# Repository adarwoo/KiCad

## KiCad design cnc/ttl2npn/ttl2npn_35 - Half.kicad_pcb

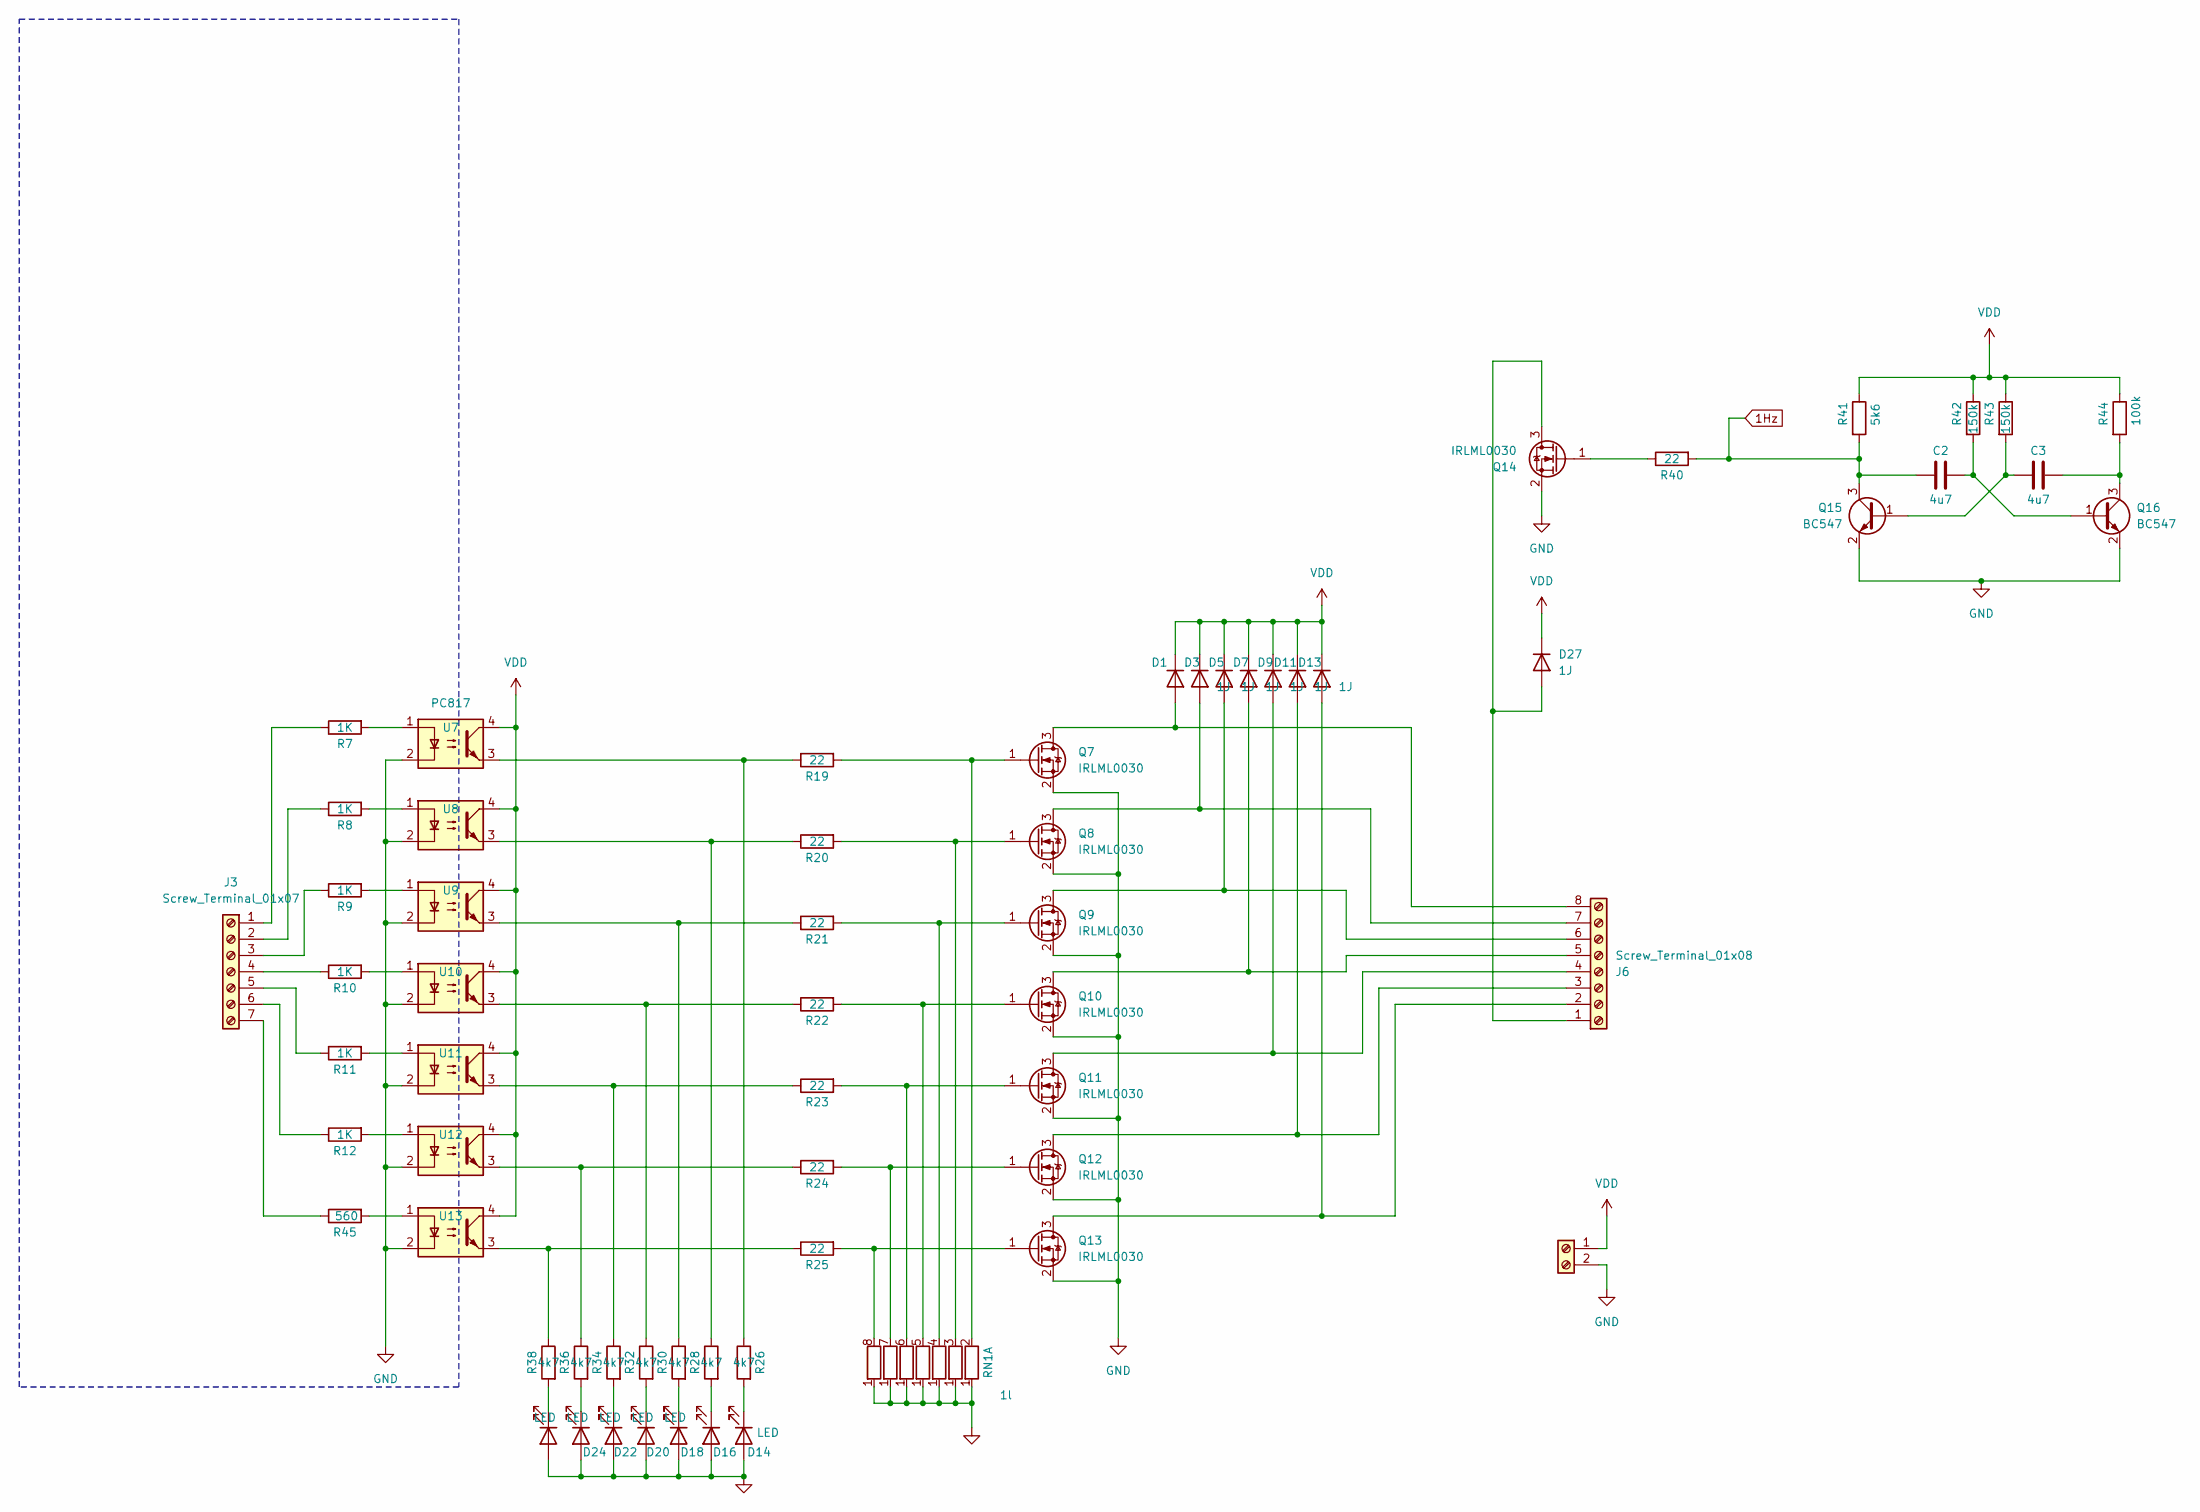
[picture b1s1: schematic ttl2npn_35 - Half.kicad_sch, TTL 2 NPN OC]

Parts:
C2, C3: 4u7; C_1206_3216Metric
D1, D3, D5, D7, D9, D11, D13, D27: 1J; D_MicroSMP_AK
D14, D16, D18, D20, D22, D24, D26: LED; LED_D3.0mm
J3: Screw_Terminal_01x07; PhoenixContact_MCV_1,5_7-G-3.81_1x07_P3.81mm_Vertical
J4: Screw_Terminal_01x02; PhoenixContact_MCV_1,5_2-G-3.81_1x02_P3.81mm_Vertical
J6: Screw_Terminal_01x08; PhoenixContact_MCV_1,5_8-G-3.81_1x08_P3.81mm_Vertical
Q7, Q8, Q9, Q10, Q11, Q12, Q13, Q14: IRLML0030; SOT-23
Q15, Q16: BC547; SOT-23
R7, R8, R9, R10, R11, R12: 1K; R_0805_2012Metric
R19, R20, R21, R22, R23, R24, R25, R40: 22; R_0805_2012Metric
R26, R28, R30, R32, R34, R36, R38: 4k7; R_0805_2012Metric
R41: 5k6; R_0805_2012Metric
R42, R43: 150k; R_0805_2012Metric
R44: 100k; R_0805_2012Metric
R45: 560; R_0805_2012Metric
RN1: 1l; R_Array_SIP8
U7, U8, U9, U10, U11, U12, U13: PC817; DIP-4_W7.62mm

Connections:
1Hz: C2.1, Q15.3 (C), R40.2, R41.2
GND: D14.2 (A), D16.2 (A), D18.2 (A), D20.2 (A), D22.2 (A), D24.2 (A), D26.2 (A), J4.2, Q7.2 (S), Q8.2 (S), Q9.2 (S), Q10.2 (S), Q11.2 (S), Q12.2 (S), Q13.2 (S), Q14.2 (S), Q15.2 (E), Q16.2 (E), RN1.1 (R1), U7.2, U8.2, U9.2, U10.2, U11.2, U12.2, U13.2
unnamed: D1.2 (A), J6.8, Q7.3 (D)
unnamed: D3.2 (A), J6.7, Q8.3 (D)
unnamed: D5.2 (A), J6.6, Q9.3 (D)
unnamed: D7.2 (A), J6.5, Q10.3 (D)
unnamed: D9.2 (A), J6.4, Q11.3 (D)
unnamed: D11.2 (A), J6.3, Q12.3 (D)
unnamed: D13.2 (A), J6.2, Q13.3 (D)
unnamed: D14.1 (K), R26.2
unnamed: D16.1 (K), R28.2
unnamed: D18.1 (K), R30.2
unnamed: D20.1 (K), R32.2
unnamed: D22.1 (K), R34.2
unnamed: D24.1 (K), R36.2
unnamed: D26.1 (K), R38.2
unnamed: D27.2 (A), J6.1, Q14.3 (D)
unnamed: J3.1, R7.1
unnamed: J3.2, R8.1
unnamed: J3.3, R9.1
unnamed: J3.4, R10.1
unnamed: J3.5, R11.1
unnamed: J3.6, R12.1
unnamed: J3.7, R45.1
unnamed: Q7.1 (G), R19.2, RN1.2 (R1.2)
unnamed: Q8.1 (G), R20.2, RN1.3 (R2.2)
unnamed: Q9.1 (G), R21.2, RN1.4 (R3.2)
unnamed: Q10.1 (G), R22.2, RN1.5 (R4.2)
unnamed: Q11.1 (G), R23.2, RN1.6 (R5.2)
unnamed: Q12.1 (G), R24.2, RN1.7 (R6.2)
unnamed: Q13.1 (G), R25.2, RN1.8 (R7.2)
unnamed: Q14.1 (G), R40.1
unnamed: C3.1, Q15.1 (B), R43.2
unnamed: C2.2, Q16.1 (B), R42.2
unnamed: C3.2, Q16.3 (C), R44.2
unnamed: R7.2, U7.1
unnamed: R8.2, U8.1
unnamed: R9.2, U9.1
unnamed: R10.2, U10.1
unnamed: R11.2, U11.1
unnamed: R12.2, U12.1
unnamed: R19.1, R26.1, U7.3
unnamed: R20.1, R28.1, U8.3
unnamed: R21.1, R30.1, U9.3
unnamed: R22.1, R32.1, U10.3
unnamed: R23.1, R34.1, U11.3
unnamed: R24.1, R36.1, U12.3
unnamed: R25.1, R38.1, U13.3
unnamed: R45.2, U13.1
VDD: D1.1 (K), D3.1 (K), D5.1 (K), D7.1 (K), D9.1 (K), D11.1 (K), D13.1 (K), D27.1 (K), J4.1, R41.1, R42.1, R43.1, R44.1, U7.4, U8.4, U9.4, U10.4, U11.4, U12.4, U13.4

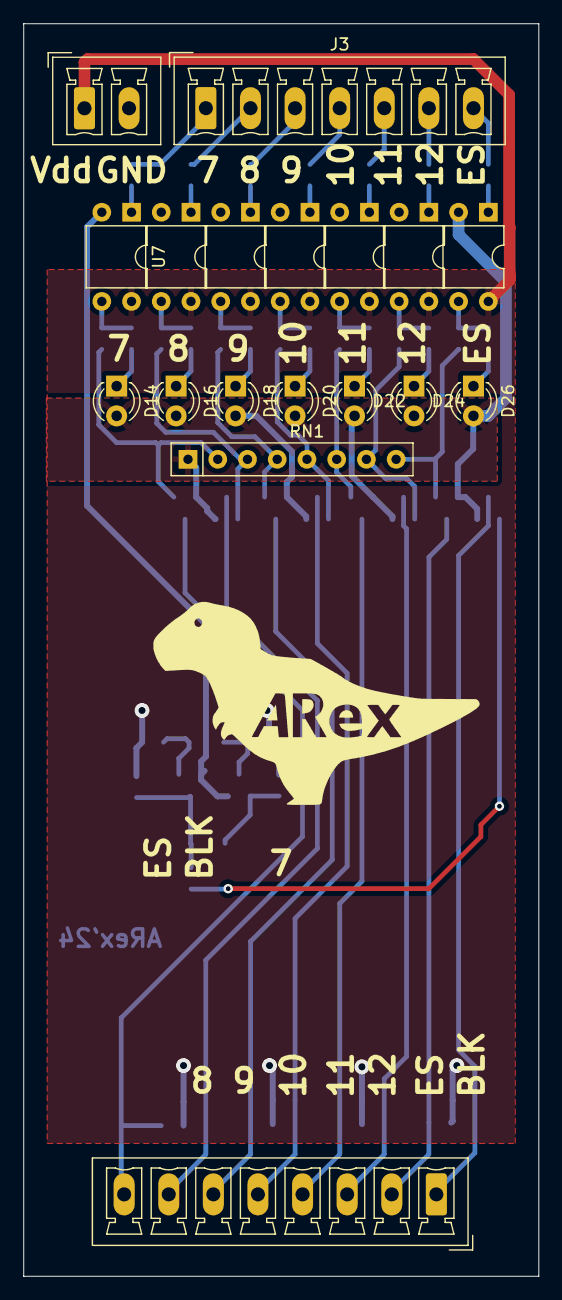
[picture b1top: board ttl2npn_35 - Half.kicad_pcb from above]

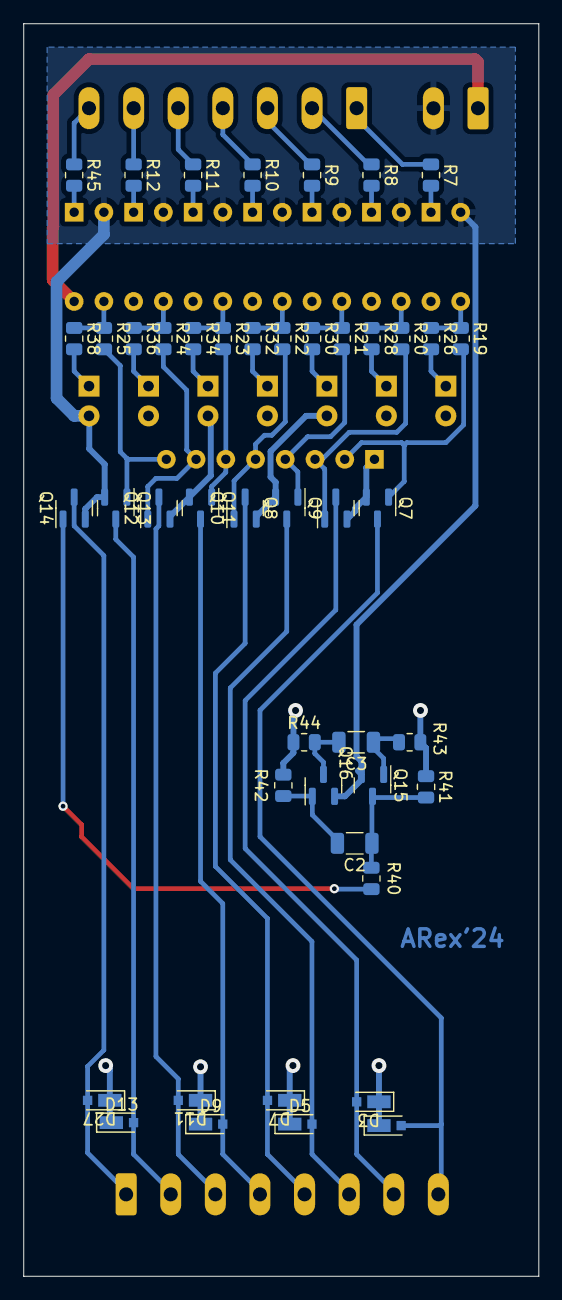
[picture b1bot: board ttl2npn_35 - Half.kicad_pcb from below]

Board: 2 copper layers, 44.0 x 107.0 mm, 64 parts (46 on the bottom side), 50 nets.

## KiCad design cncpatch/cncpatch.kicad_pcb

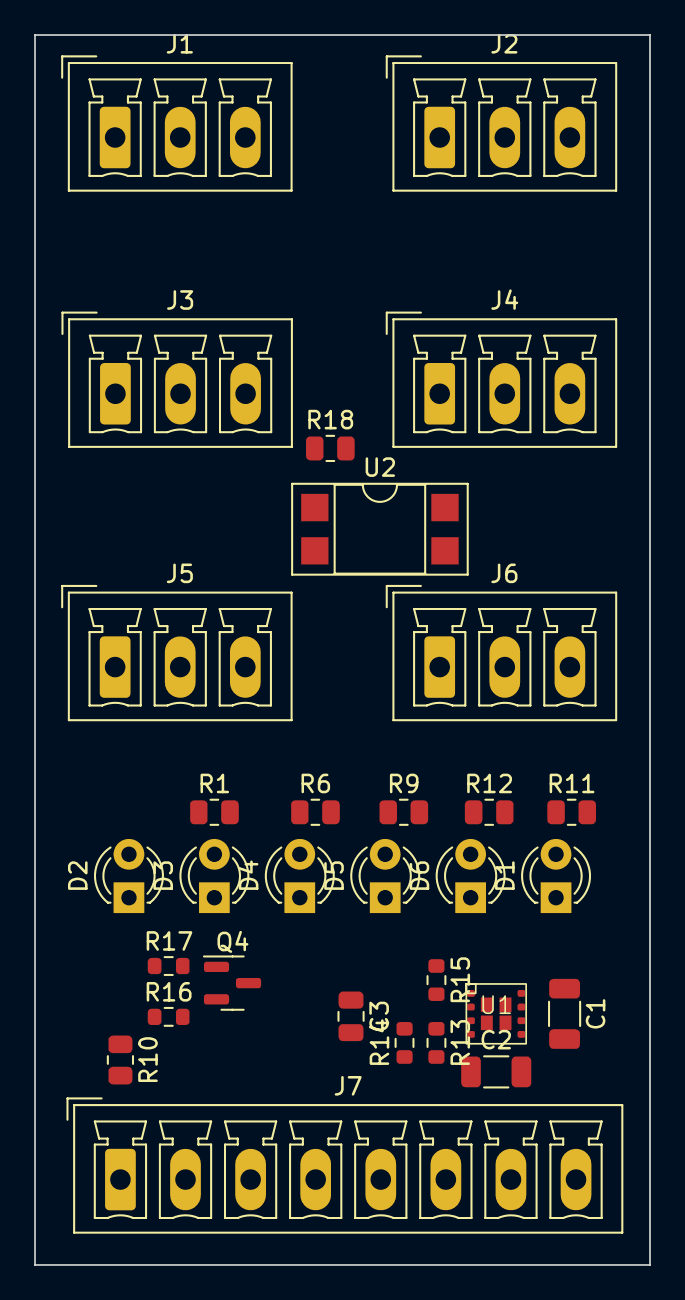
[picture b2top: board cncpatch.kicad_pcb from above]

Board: 2 copper layers, 36.0 x 72.0 mm, 31 parts (0 on the bottom side), 23 nets, no tracks yet.

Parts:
C1, C2: 22u; C_1206_3216Metric
C3: 3n3; C_0805_2012Metric
D1: RED; LED_D3.0mm
D2: LED; LED_D3.0mm
D3, D4, D5: GRN; LED_D3.0mm
D6: ORG; LED_D3.0mm
J1, J2, J3, J4, J5, J6: Conn_01x03_Socket; PhoenixContact_MCV_1,5_3-G-3.81_1x03_P3.81mm_Vertical
J7: Conn_01x08_Socket; PhoenixContact_MCV_1,5_8-G-3.81_1x08_P3.81mm_Vertical
Q4: AO3401A; SOT-23
R1, R6, R9, R10, R11, R18: 10k; R_0805_2012Metric
R12: 3k3; R_0805_2012Metric
R13, R16: 10k; R_0603_1608Metric
R14: 232k; R_0603_1608Metric
R15: 44k2; R_0603_1608Metric
R17: 22; R_0603_1608Metric
U1: MicroSiP
U2: PC817; DIP-4_W7.62mm_SMDSocket_SmallPads

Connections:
+5V: C2.1, J6.1, Q4.2 (S), R12.2, R13.2, R14.1, U1.4 (VOUT), U1.6 (VOS)
/LASER_EN: J6.2, Q4.3 (D)
/LASER_ON_OC: J7.7, R16.1, R17.1
/SPINDLE_STOP: J7.8, U2.4
/SPINDLE_STOP_OC: J2.2, U2.2
/TOUCH_OUT: D1.1 (K), J4.2, J7.6
/X_MASSO: J1.2, J7.3, R1.2
/Y_MASSO: J3.2, J7.4, R6.2
/Z_MASSO: J5.2, J7.5, R9.2
GND: C1.2, C2.2, C3.2, D2.1 (K), D3.1 (K), D4.1 (K), D5.1 (K), D6.1 (K), J1.3, J2.3, J3.3, J4.3, J5.3, J6.3, J7.2, R15.1, U1.5 (GND), U1.9 (GND), U2.3
unnamed: D1.2 (A), R11.1
unnamed: D2.2 (A), R10.1
unnamed: D3.2 (A), R1.1
unnamed: D4.2 (A), R6.1
unnamed: D5.2 (A), R9.1
unnamed: D6.2 (A), R12.1
unnamed: Q4.1 (G), R17.2
unnamed: R18.1, U2.1
unnamed: C1.1, U1.7 (EN), U1.8 (VIN)
unnamed: R14.2, R15.2, U1.2 (FB)
unnamed: R13.1, U1.3 (PG)
unnamed: C3.1, U1.1 (SS)
VDD: J1.1, J2.1, J3.1, J4.1, J5.1, J7.1, R10.2, R11.2, R16.2, R18.2

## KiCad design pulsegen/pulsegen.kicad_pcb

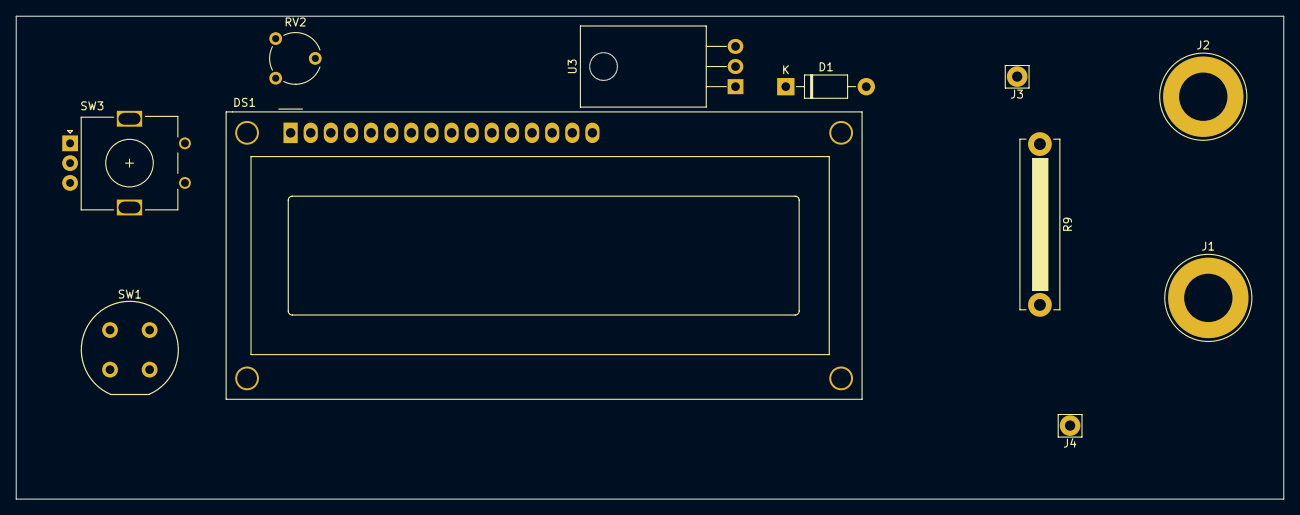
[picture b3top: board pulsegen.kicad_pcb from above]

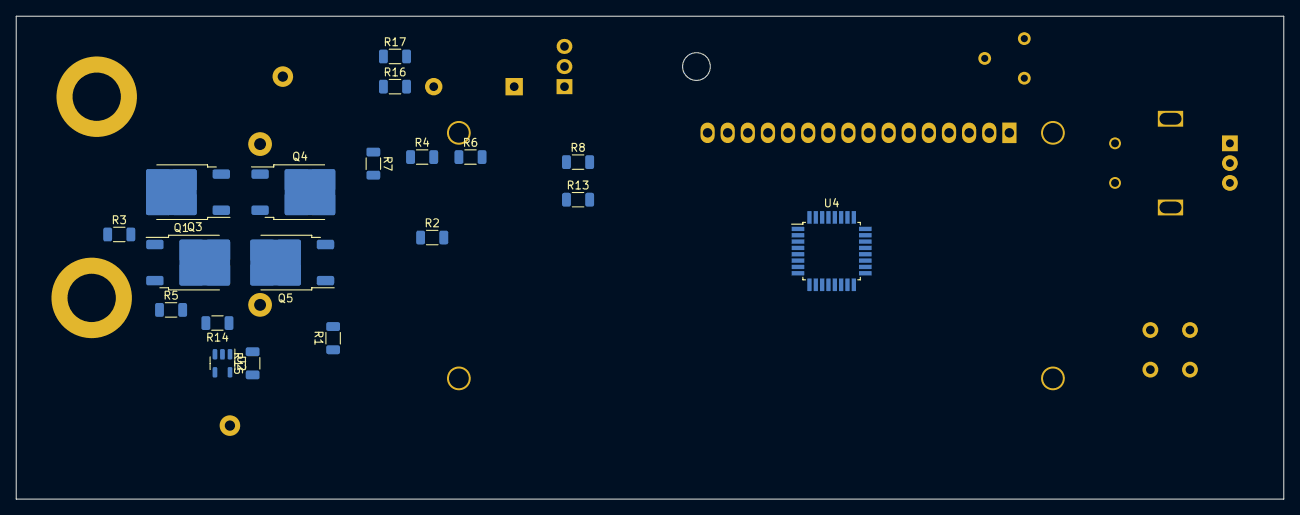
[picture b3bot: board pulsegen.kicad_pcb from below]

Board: 2 copper layers, 160.0 x 61.0 mm, 30 parts (19 on the bottom side), 31 nets, no tracks yet.

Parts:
D1: 1N4007; D_DO-41_SOD81_P10.16mm_Horizontal
DS1: WC1602A
J1, J2: Screw_Terminal_01x01; Banana_Jack_1Pin
J3, J4: Screw_Terminal_01x01; Pin_D1.3mm_L11.3mm_W2.8mm_Flat
Q1, Q4: QM6006D; TO-252-2
Q3, Q5: QM6015D; TO-252-2
R1, R2, R3, R4: 22; R_1206_3216Metric
R5, R6, R7, R8: 10k; R_1206_3216Metric
R9: 0.01 5W; R_Bare_Metal_Element_L21.3mm_W4.8mm_P20.30mm
R13, R15: 1k; R_1206_3216Metric
R14: 100k; R_1206_3216Metric
R16, R17: R; R_1206_3216Metric
RV2: R_Potentiometer; Potentiometer_Piher_PT-6-V_Vertical
SW1: SW_Push; Push_E-Switch_KS01Q01
SW3: RotaryEncoder_Switch; RotaryEncoder_Alps_EC11E_Vertical_H20mm
U2: MCP6001R; SOT-23-5
U3: LM7805_TO220; TO-220-3_Horizontal_TabDown
U4: ATmega328-A; TQFP-32_7x7mm_P0.8mm

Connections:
/LCD.D4: DS1.11 (D4), U4.26 (PC3)
/LCD.D5: DS1.12 (D5), U4.27 (PC4)
/LCD.D6: DS1.13 (D6), U4.28 (PC5)
/LCD.D7: DS1.14 (D7), U4.29 (~RESET/PC6)
/LCD.E: DS1.6 (E), U4.23 (PC0)
/LCD.RS: DS1.4 (RS), U4.25 (PC2)
/LCD.R/~W: DS1.5 (R/W), U4.24 (PC1)
GND: DS1.1 (VSS), J4.1, R6.1, R7.1, R9.2, R13.1, RV2.3, SW1.2, U2.5 (V-), U3.2 (GND), U4.3 (GND), U4.5 (GND), U4.21 (GND)
Ismooth: R15.1, U4.22 (ADC7)
unnamed: D1.2 (A), R16.2, R17.2
unnamed: D1.1 (K), U3.1 (VI)
unnamed: DS1.3 (VO), RV2.2
unnamed: J1.1, Q4.2 (D), Q5.3 (S)
unnamed: J2.1, Q1.2 (D), Q3.3 (S)
unnamed: Q1.1 (G), R4.1
unnamed: Q1.3 (S), Q4.3 (S), R9.1, U2.3 (+)
unnamed: Q3.1 (G), R3.1
unnamed: Q4.1 (G), R2.2
unnamed: Q5.1 (G), R1.2
unnamed: R14.1, R15.2, U2.1
unnamed: R13.2, R14.2, U2.4 (-)
unnamed: R3.2, R5.1, U4.12 (PB0)
unnamed: R1.1, R8.1, U4.13 (PB1)
unnamed: R4.2, R6.2, U4.14 (PB2)
unnamed: SW1.1, U4.30 (PD0)
unnamed: SW3.A, U4.32 (PD2)
unnamed: SW3.C, U4.1 (PD3)
unnamed: SW3.B, U4.2 (PD4)
unnamed: R2.1, R7.2, U4.10 (PD6)
VCC: DS1.2 (VDD), RV2.1, U2.2 (V+), U4.4 (VCC), U4.6 (VCC)
VDD: J3.1, Q3.2 (D), Q5.2 (D), R5.2, R8.2, R16.1, R17.1
